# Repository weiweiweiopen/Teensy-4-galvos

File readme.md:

# Teensy-4-galvos

DIY laser galvanometer projector tools for Teensy 4.0, Max/MSP, and Python-based XY path generation. The system was developed for the [Laser Dye Project](https://shihweichieh.com/Laser-Dye-Project), but it can also be used for engraving, PCB work, and audio-visual experiments.

## Quick Start

1. Clone the repository.
2. Flash the Teensy 4.0 firmware from `src/`.
3. Open the Max patch in `max/` and select the Teensy audio device. Or use the Python tools in `python/`.

## Python Tools

The main GUI app is `python/ld_stippling_qt.py`.

Setup on Mac and Linux:

```bash
python3 -m venv .venv
source .venv/bin/activate
python -m pip install -r python/requirements.txt
python python/ld_stippling_qt.py
```

Windows:

```bash
python -m venv .venv
.venv\Scripts\activate
pip install -r python\requirements.txt
python python\ld_stippling_qt.py
```

Notes:

- Use native Windows Python for audio output; WSL may not see the laser audio device correctly.
- `scipy` is recommended for fast Voronoi rendering on large images.
- `sounddevice` is only needed for direct audio playback from the Python GUI.

you may purchase the ready made machine here: https://weiweiweishop2.myshopify.com/

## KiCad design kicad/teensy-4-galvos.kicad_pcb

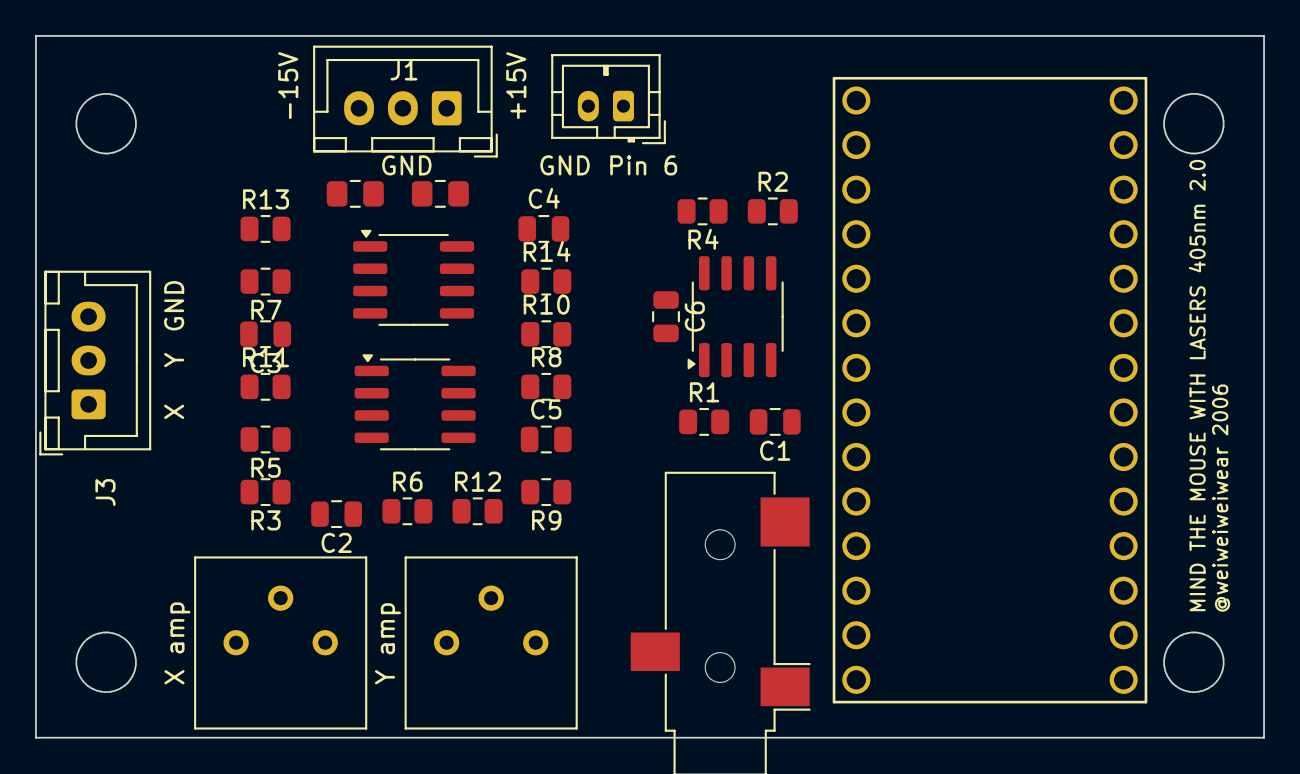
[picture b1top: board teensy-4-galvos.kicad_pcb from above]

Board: 2 copper layers, 70.0 x 40.0 mm, 32 parts (0 on the bottom side), 22 nets, no tracks yet.

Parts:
C1, C2, C3, C4, C5, C6: 0.1uF; C_0805_2012Metric
C7, C8: 10uF; C_0805_2012Metric_Pad1.18x1.45mm_HandSolder
J1, J3: +15 G -15; JST_XH_B3B-XH-A_1x03_P2.50mm_Vertical
J2: AudioJack3_SwitchTR; Jack_3.5mm_CUI_SJ-3523-SMT_Horizontal
J7: 405nm; JST_PH_B2B-PH-K_1x02_P2.00mm_Vertical
R1, R2, R5, R7: 1k; R_0805_2012Metric
R3, R4, R11, R12, R13, R14: 330; R_0805_2012Metric
R6, R8, R9, R10: 22k; R_0805_2012Metric
U1: TL072; SOIC-8_3.9x4.9mm_P1.27mm
U2: X galvo; SOIC-8_3.9x4.9mm_P1.27mm
U3: Y TL072; SOIC-8_3.9x4.9mm_P1.27mm
U4: Teensy4.0; Teensy40
X amp: 10k; Potentiometer_Bourns_3386P_Vertical
Y amp: 10k; Potentiometer_Bourns_3386P_Vertical

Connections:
+15V: C4.1, C5.1, C6.1, C8.1, J1.1, U1.8 (V+), U2.8 (V+), U3.8 (V+)
-15V: C1.1, C2.1, C3.1, C7.1, J1.3, U1.4 (V-), U2.4 (V-), U3.4 (V-)
/laser en: J7.1, U4.8 (6_OUT1D)
Ax_Ring_OUT: J2.R, U1.5 (+)
Ax_Tip_OUT: J2.T, U1.3 (+)
GND: C1.2, C2.2, C3.2, C4.2, C5.2, C6.2, C7.2, C8.2, J1.2, J3.3, J7.2, R1.1, R2.1, U2.5 (+), U3.5 (+)
unnamed: J3.1, R12.1
unnamed: J3.2, R14.1
unnamed: R3.1, R5.2, R6.2, U1.1
unnamed: R3.2, X amp.2
unnamed: R4.1, R7.2, R8.2, U1.7
unnamed: R4.2, Y amp.2
unnamed: R10.1, R14.2, U3.7
unnamed: R9.1, R12.2, U2.7
unnamed: R1.2, U1.2 (-), X amp.1
unnamed: R2.2, U1.6 (-), Y amp.1
unnamed: R5.1, U2.3 (+)
unnamed: R11.2, U2.1, U2.2 (-)
unnamed: R6.1, R9.2, U2.6 (-)
unnamed: R7.1, U3.3 (+)
unnamed: R13.2, U3.1, U3.2 (-)
unnamed: R8.1, R10.2, U3.6 (-)

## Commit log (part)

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2025-03-31 Create max patches
2025-09-06 update laser_pin to 5 from 6
2025-09-14 Initial import: Teensy-4-galvos project; add FreeCAD image to README
2025-12-26 Add files via upload
    fixed the laser on/off problem while switching mode
2026-02-11 Change laserPin from 5 to 6
2026-03-15 Add Teensy galvo project with Python stippling tools
2026-03-15 Remove generated cache and lock files
2026-03-15 Rename Python tools folder and remove old stub
2026-03-26 Update README with concise setup guide
2026-03-26 Stabilize Python tools setup and rendering
2026-03-26 Change Teensy version from 4.1 to 4.0
    Updated references from Teensy 4.1 to Teensy 4.0 in the README.
2026-04-07 Refresh Python GUI with classic Mac styling
2026-06-05 Update readme.md
    Added shop link
2026-06-06 Update KiCad source files
2026-06-08 Update KiCad board files
